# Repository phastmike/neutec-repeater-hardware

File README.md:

# Guia do projecto Repetidor Neutec

Este documento visa guiar e documentar o projecto Repetidor Neutec.

## Enquadramento

O projecto surge de um contacto informal do Costa (**CT1EYN**) comigo
(**CT1ENQ**), cujo objectivo inicial seria documentar a parte de controlo que o
Costa (**CT4QC**) fez no repetidor de UHF de Guimarães para posteriormente as 
aplicar num repetidor de origem da Neutec que não cumpria os requisitos legais.

Quando referimos o Costa (**CT4QC**), também devemos incluir o Armindo
(**CT1AND**) e outros que eventualmente tenham participado no esforço de munir a
ARM (Associação de Rádioamadores do Minho) de um conjunto de repetidores de
"construção caseira".

Como não privei nem tive grande contacto com os membros da ARM desse período,
além de ter estado ausente da região por vários anos, acabo por desconhecer a
história dos bastidores técnicos da associação. Entretanto, infelizmente, quem 
detinha o conhecimento acabou por falecer (sk).

### Um pouco de história

Através de um documento anexo ao repetidor de Guimarães conseguimos apurar a
data de Setembro 1998 pelo que terá sido por essa altura que o repetidor estaria
pronto para ser instalado. Este repetidor era um rádio Neutec SM-1630U (UHF)
modificado para servir como repetidor. O emissor e receptor funcionam em
simultâneo e essa modificação não foi documentada, nem na altura, nem agora.
Também foi introduzida alguma electrónica para controlo de transmissão, 
identificação em morse com intervalo de 10 minutos entre outros.
Posteriormente, teve nova intervenção para cumprir os novos requisitos de
identificação de voz. Estas adições são o alvo da nossa documentação.

Inicialmente o indicativo do repetidor era **CT0UGM** na frequência de 
**439.100 MHz**, RU88, e com a alteração da legislação, passou a ter o
indicativo **CQ0UGMR**, RU728, até aos dias de hoje.

### O início do projecto

Volvidos estes anos todos e havendo no legado da ARM, um repetidor de origem da
Neutec (SM-1645HS) para os 2m (VHF), operacional mas sem tom de protecção e sem 
identificação, fazia todo o sentido perceber o que foi feito no repetidor de 
Guimarães e replicar, dentro das diferenças existentes, algo similar para dotar
a ARM de um repetidor que pudesse servir de substituto ou mesmo para uma nova
instalação. 

Havendo essa necessidade e com a pandemia que nos afectou desde 2019 até à
actualidade (estamos em 2021) houve um novo fôlego na comunidade de 
rádioaamadores e o Costa (**CT1EYN**) lançou o desafio que foi aceite.

Infelizmente só tivemos acesso ao repetidor Neutec já na fase final do projecto
pelo que haveria lugar a algumas melhorias adicionais, ainda assim, foi obtido
um bom resultado e estamos em testes finais faltando apenas os testes de campo
na montanha da Santa Marta, no local do repetidor.

## Requisitos

Legalmente, em Portugal, um repetidor para o serviço de amador deve cumprir um
conjunto de requisitos. Do ponto de vista de controlo, são os seguintes:

- Tempo de retransmissão - Timeout Timer: Max 3 min (180s)
- Tempo de penalização - Retrigger/Penalty: 5 seg.
- Intervalo de identificação - ID Interval: Max 10 min (600s)

Requisito adicional, será o de evitar que a identificação ocorra quando alguém
está a utilizar o repetidor evitando assim que duas vozes concorram pela atenção
. Além disso deve contemplar a utilização do microfone de mão, no próprio
repetidor e evitar que não haja identificação durante um período de bloqueio
("timeout"). Este requisito levanta uma questão em particular, a da
obrigatoriedade de se identificar de 10 em 10 minutos. No entanto, a lei deve,
na minha opinião, ser entendida ao invés de uma interpretação cega. Assim; 
do ponto de vista da nossa actividade, faz todo o sentido, identificar o
repetidor, intervaladamente, para que eventuais escutas,quando não haja 
actividade no repetidor, consigam identificar o mesmo.
Se a identificação ocorrer em simultâneo com um QSO, em nada será benéfico, 
tanto é que este requisito se coloca. Do ponto de vista informativo, a presença
de um QSO implica a identificação dos intervinientes que por sua vez identifica
indirectamente o repetidor que por sua vez aguardará de forma incessante, a
possibilidade de se identificar, se é que podemos dizê-lo desta forma. Se a 
identificação ocorre no primeiro instante em que está livre ou se após uma
análise mais ou menos cuidada, o resultado obtido, será sempre no intuito de
seguir a lei mas salvaguardando a "qualidade" de um qso.

## Primeira análise

O primeiro passo do projecto foi efectuar engenharia reversa nos circuitos de
controlo construídos pelo Costa (**CT4QC**) por forma a desenhar um esquema e
posterior compreensão dos passos dados na altura. 

O repetidor de Guimarães foi construído com montagem de superfície utilizando
componentes THT, com PCB cortados "à mão" e placas de furos genéricas. Além
disso, estão divididos em dois "conjuntos" que para simplicidade passaremos a
designar por:

- Placa de cima
- Placa de baixo

Esta designação tem em consideração o posicionamente dos circuitos na montagem
original que foi mantida.

### Placa de baixo

Na placa de baixo temos vários blocos:

- Detecção de sub-tom
- Controlo de PTT
- Temporização de cauda
- Temporização de retransmissão

### Placa de cima

Na placa de cima temos os blocos referentes à identificação:

- microcontrolador
 - temporizador de 10min.
 - verificação de tom e ou PTT
 - disparo da identificação Voz/Morse
- controlo de PTT da identificação
- gerador de sinal áudio de Morse

## Organização do projecto

Após esta breve explicação, convém descrever a organização da documentação
relativa ao projecto. 

O projecto é na realidade um conjunto de projectos:

- Desenho dos esquemas do repetidor original
- Novo projecto de repetidor baseado no anterior, inclui PCBs e novo *firmware*
- Adaptação do desenho original, no repetidor de Guimarães com as alterações
realizadas ao esquema inicial.
- Vários (documentos, *datasheets*, imagens, etc)

## Descrição detalhada

Segue uma descrição, mais detalhada, das várias pastas deste projecto.

### [CT1ENQ_CT1EYN](./CT1ENQ_CT1EYN/)

As novas placas, esquemas e firmware.

- [Placa de baixo](./CT1ENQ_CT1EYN/bottom)
- [Placa de cima](./CT1ENQ_CT1EYN/top)
- [Novo firmware e código fonte (AT89C2051)](./CT1ENQ_CT1EYN/firmware)
- [Manual](./CT1ENQ_CT1EYN/manual)

### [CT4QC](./CT4QC)

O esquema original das adições que foram feitas ao SM-1630U para o dotar de
controlo de repetidor (baseado no repetidor de UHF de Guimarães). Também inclui
os esquemas das alterações que foram feitas ao original e uma "imagem" do
código original (binário). O firmware para esta modificação está anexa ao
novo *firmware* do repetidor.

- [Esquema de baixo](./CT4QC/original/bottom)
- [Esquema de cima](./CT4QC/original/top)
- [Esquema das novas modificações (cima)](./CT4QC/mod/)
- [*Firmware* original do AT89C2051](./CT4QC/original/firmware)

#### [Tools](./tools)

Programas auxiliares para cálculo de valores no temporizador e detector de tom.
Contém tabelas de valores em pdf.

#### [Doc](./doc/)
  
Conjunto de documentos reunidos durante o desenrolar do projecto, uns mais
relevantes do que outros (Datasheets, Papers, Pdfs, etc).

**Esta pasta não deverá estar presente nos repositórios públicos**.

#### [Images](./images/)

Imagens relacionadas com o projecto.

**Esta pasta não deverá estar presente nos repositórios públicos**.

#### [Sound](./sound/)

Ficheiros de áudio, utilizados no projecto (identificação).

## Software, *Frameworks* e outras informações

O trabalho foi projectado na sua totalidade num sistema Linux (Fedora 34) no
entanto existem as mesmas ferramentas ou equivalentes para o sistema Windows.

No desenho de esquemas e placas de circuito impresso, foi utilizado o
software gratuito, [KiCad 5.1.10-1](https://www.kicad.org).

O firmware foi desenvolvido em linguagem C e foi utilizado o compilador **sdcc**
, [Small Devices C Compiler](http://sdcc.sourceforge.net/) (v4.0.0) juntamente
com **Makefiles**.

Para programar o microcontrolador AT89C2051, utilizamos o programador
[TL866II Plus](http://www.autoelectric.cn/en/tl866_main.html) e o programa
[**minipro** (linux)](https://gitlab.com/DavidGriffith/minipro/).

## Notas finais

Os projectos devem ter documentos descritivos dentro de cada pasta, sempre que
se justificar.

Também convém indicar que o projecto de firmare (código fonte), quando num
contexto de repositório público, terá o seu repositório próprio. Já os esquemas
e restantes ficheiros estarão a acompanhar este documento. Num contexto interno
à ARM ou da comunidade de rádioamadores local, os ficheiros estarão todos 
agregados, num formato de compressão comum.

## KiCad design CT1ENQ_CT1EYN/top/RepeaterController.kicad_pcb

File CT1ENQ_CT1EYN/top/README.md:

# Neutec Repetidor/Repeater

## PCB Assembly and fitting notes

After assembly, Costa's 555 (Motorola) was erratic at best (bad pin connection?). Changed it for a Philips one and problem solved. Repeater was not ungrabbing the PTT line at the end of transmition (id). The PTT sense circuit is very sensible. Adding a 100nf/10nf capacitor at the main J connector (8 pin molex) pin1 (ID_PTT) did improve the result. Also the ISD play auto ptt key up saw the 100uf removed. Probably it's not even needed or if added then a lower value, eventually a ceramic cap would suffice.

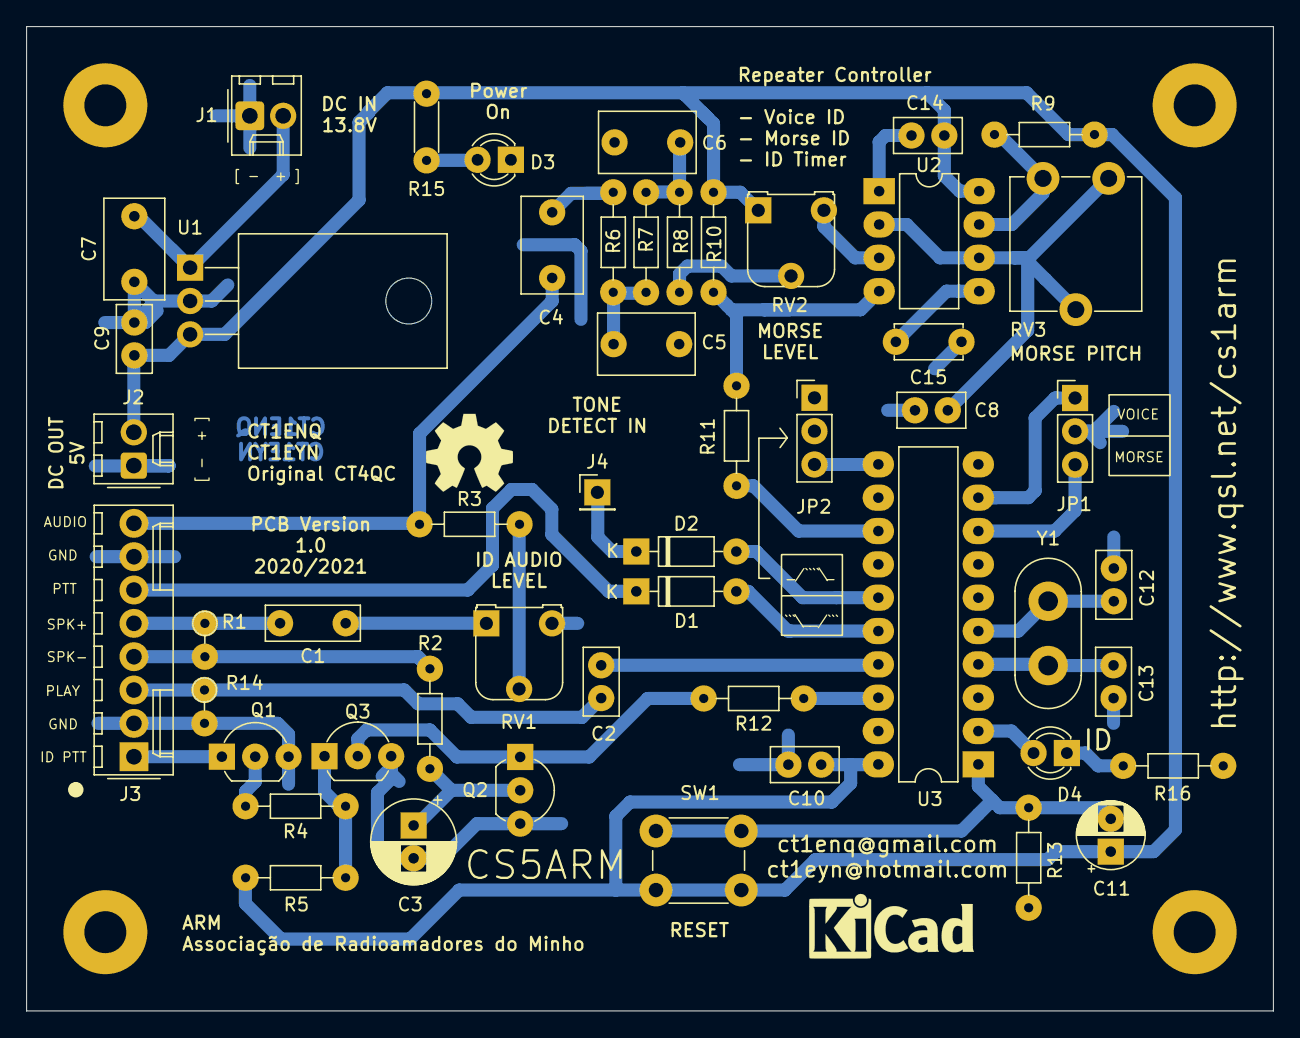
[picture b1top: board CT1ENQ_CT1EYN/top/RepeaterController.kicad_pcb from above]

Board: 2 copper layers, 95.0 x 75.0 mm, 52 parts (0 on the bottom side), 39 nets.

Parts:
C1: 4n7; C_Disc_D7.0mm_W2.5mm_P5.00mm
C2, C8, C9, C10, C14: 100n; C_Disc_D5.0mm_W2.5mm_P2.50mm
C3: 100u/16V; CP_Radial_D6.3mm_P2.50mm
C4, C5, C6: 22n; C_Rect_L7.2mm_W4.5mm_P5.00mm_FKS2_FKP2_MKS2_MKP2
C7: 470n; C_Disc_D7.5mm_W4.4mm_P5.00mm
C11: 10u/50V; CP_Radial_D5.0mm_P2.50mm
C12, C13: 33p; C_Disc_D5.0mm_W2.5mm_P2.50mm
C15: 10n; C_Disc_D5.0mm_W2.5mm_P5.00mm
D1, D2: 1N4148; D_DO-35_SOD27_P7.62mm_Horizontal
D3, D4: LED; LED_D3.0mm
J1, J2: Conn_01x02; Molex_KK-254_AE-6410-02A_1x02_P2.54mm_Vertical
J3: Conn_01x08; Molex_KK-254_AE-6410-08A_1x08_P2.54mm_Vertical
J4: Tone Detector; PinHeader_1x01_P2.54mm_Vertical
JP1: ID TYPE(None/Either/Both?); PinHeader_1x03_P2.54mm_Vertical
JP2: PLAY L2H or H2L; PinHeader_1x03_P2.54mm_Vertical
Q1: BC548B; TO-92_Inline_Wide
Q2: BC548; TO-92_Inline_Wide
Q3: BC548C; TO-92_Inline_Wide
R1: 27; R_Axial_DIN0204_L3.6mm_D1.6mm_P2.54mm_Vertical
R2, R16: 1k; R_Axial_DIN0204_L3.6mm_D1.6mm_P7.62mm_Horizontal
R3, R9: 10k; R_Axial_DIN0204_L3.6mm_D1.6mm_P7.62mm_Horizontal
R4: 3k9; R_Axial_DIN0204_L3.6mm_D1.6mm_P7.62mm_Horizontal
R5, R10: 4k7; R_Axial_DIN0204_L3.6mm_D1.6mm_P7.62mm_Horizontal
R6: 680; R_Axial_DIN0204_L3.6mm_D1.6mm_P7.62mm_Horizontal
R7, R8: 820; R_Axial_DIN0204_L3.6mm_D1.6mm_P7.62mm_Horizontal
R11: 120; R_Axial_DIN0204_L3.6mm_D1.6mm_P7.62mm_Horizontal
R12: 4K7; R_Axial_DIN0204_L3.6mm_D1.6mm_P7.62mm_Horizontal
R13: 8k2; R_Axial_DIN0204_L3.6mm_D1.6mm_P7.62mm_Horizontal
R14: 10k; R_Axial_DIN0204_L3.6mm_D1.6mm_P2.54mm_Vertical
R15: 1k; R_Axial_DIN0204_L3.6mm_D1.6mm_P5.08mm_Horizontal
RV1: 50k; Potentiometer_Runtron_RM-065_Vertical
RV2: 6k8; Potentiometer_Runtron_RM-065_Vertical
RV3: 22k; Potentiometer_ACP_CA9-V10_Vertical
SW1: RESET; SW_PUSH_6mm_H4.3mm
U1: L7805; TO-220-3_Horizontal_TabDown
U2: NE555P; DIP-8_W7.62mm_LongPads
U3: AT89C2051-24PU; DIP-20_W7.62mm_LongPads
Y1: 4MHz; Crystal_HC50_Vertical

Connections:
+5V: C9.2, C10.1, C11.1, C14.1, J2.2, R5.1, R9.1, R10.1, R15.1, RV2.1, SW1.2, U1.3, U2.8, U3.20
Audio: C4.1, J3.8, R3.1
GND: C3.2, C5.2, C6.2, C7.1, C8.2, C9.1, C10.2, C12.2, C13.2, C14.2, C15.2, D3.1, J1.1, J2.1, J3.2, J3.7, JP1.2, JP2.1, JP2.2, Q1.3, Q2.3, Q3.3, R13.2, R14.2, R16.2, RV1.3, U1.2, U2.1, U3.10
ID_PTT: J3.1, Q1.1
ISD_PLAY: C2.2, J3.3, R14.1
ISD_SPK+: C1.2, J3.5, R1.1
ISD_SPK-: J3.4, R1.2, R2.2
unnamed: C1.1, RV1.1
unnamed: C2.1, U3.17
unnamed: C3.1, Q2.2, R2.1
unnamed: C4.2, R6.1
unnamed: C5.1, R6.2, R7.1
unnamed: C6.1, R7.2, R8.1
unnamed: C8.1, RV3.2, RV3.3, U2.2, U2.6
unnamed: C11.2, R13.1, SW1.1, U3.1
unnamed: C12.1, U3.5, Y1.1
unnamed: C13.1, U3.4, Y1.2
unnamed: C15.1, U2.5
unnamed: D3.2, R15.2
unnamed: D4.1, R16.1
unnamed: D4.2, U3.2
unnamed: JP1.1, U3.9
unnamed: JP1.3, U3.8
unnamed: JP2.3, U3.11
unnamed: Q1.2, R4.2
unnamed: Q2.1, Q3.2, R12.2
unnamed: Q3.1, R4.1, R5.2
unnamed: R3.2, RV1.2
unnamed: R8.2, RV2.2
unnamed: R9.2, RV3.1, U2.7
unnamed: R10.2, R11.1, U2.4
unnamed: R11.2, U3.13
unnamed: R12.1, U3.18
unnamed: RV2.3, U2.3
PTT: D1.1, J3.6
PTT_IN: D1.2, U3.16
TONE_IN: D2.2, U3.15
ToneDetector: D2.1, J4.1
VCC: C7.2, J1.2, U1.1

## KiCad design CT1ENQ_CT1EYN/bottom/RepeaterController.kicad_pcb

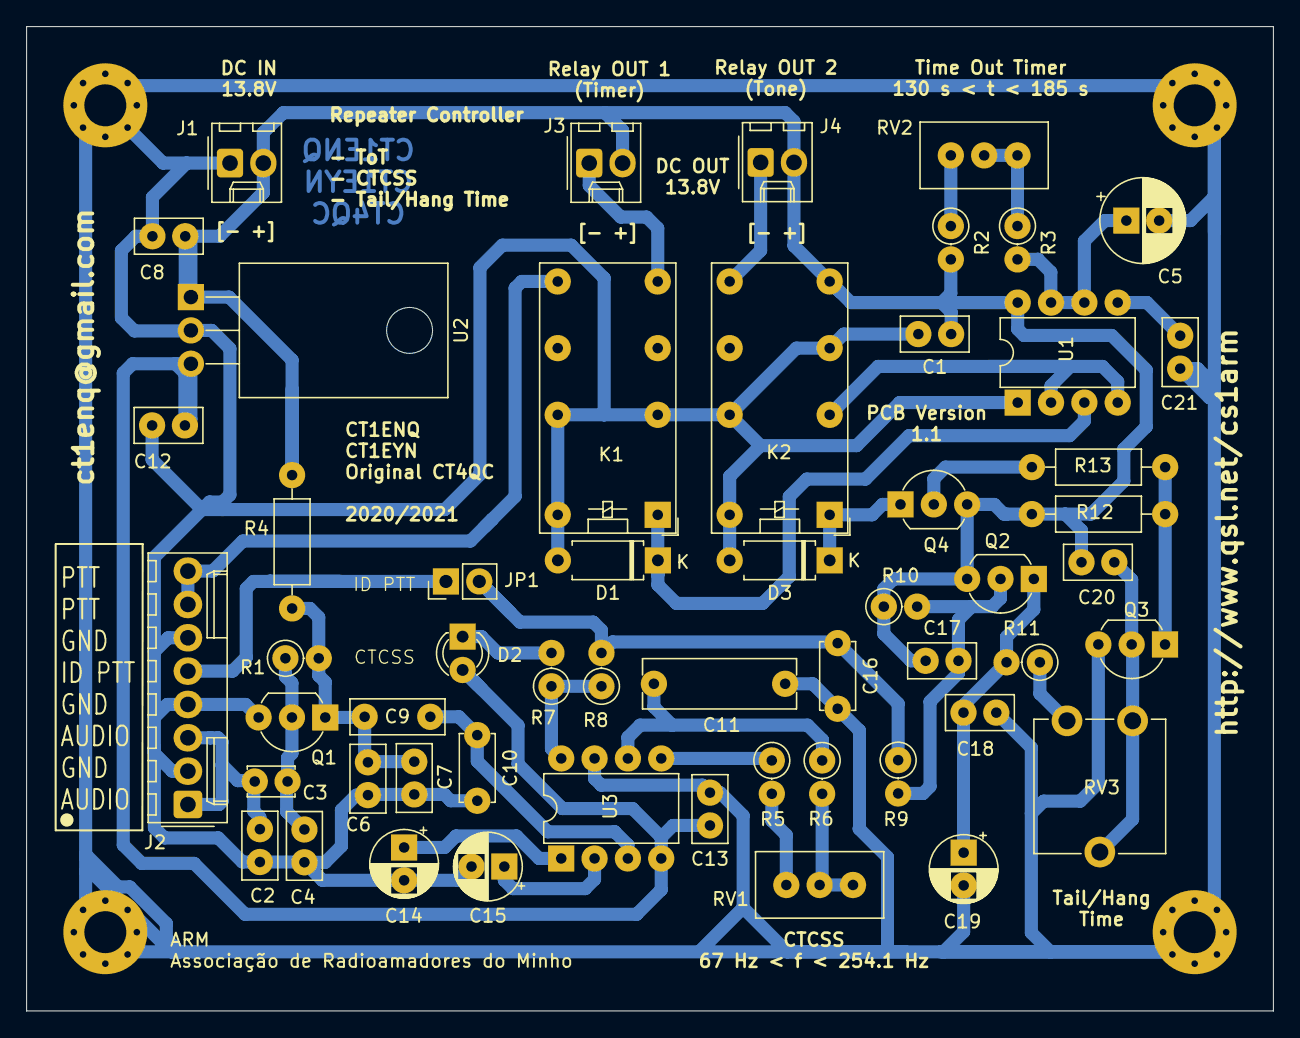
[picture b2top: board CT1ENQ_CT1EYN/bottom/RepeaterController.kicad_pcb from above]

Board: 2 copper layers, 95.0 x 75.0 mm, 54 parts (0 on the bottom side), 33 nets.

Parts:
C1, C2, C13: 330p; C_Disc_D5.0mm_W2.5mm_P2.50mm
C3: 1u; C_Disc_D3.4mm_W2.1mm_P2.50mm
C4, C7, C18, C20: 27p; C_Disc_D5.0mm_W2.5mm_P2.50mm
C5: 47u/25V; CP_Radial_D6.3mm_P2.50mm
C6: 100n; C_Disc_D5.0mm_W2.5mm_P2.50mm
C8: 0.33u; C_Disc_D5.0mm_W2.5mm_P2.50mm
C9: 470n; C_Disc_D7.0mm_W2.5mm_P5.00mm
C10: 330p; C_Disc_D5.0mm_W2.5mm_P5.00mm
C11: 100n Polyester; C_Rect_L11.5mm_W3.6mm_P10.00mm_MKT
C12: 0.1u; C_Disc_D5.0mm_W2.5mm_P2.50mm
C14: 47u/25V; CP_Radial_D5.0mm_P2.50mm
C15: 1u/25V; CP_Radial_D5.0mm_P2.50mm
C16: 27p; C_Disc_D5.0mm_W2.5mm_P5.00mm
C17: 2.2n; C_Disc_D5.0mm_W2.5mm_P2.50mm
C19: 2.2u/25V; CP_Radial_D5.0mm_P2.50mm
C21: 10n *; C_Disc_D5.0mm_W2.5mm_P2.50mm
D1, D3: 1N4148/1N4001; D_A-405_P7.62mm_Horizontal
D2: LED 3mm; LED_D3.0mm
J1, J3, J4: Conn_01x02; Molex_KK-254_AE-6410-02A_1x02_P2.54mm_Vertical
J2: Conn_01x08; Molex_KK-254_AE-6410-08A_1x08_P2.54mm_Vertical
JP1: Jumper; PinHeader_1x02_P2.54mm_Vertical
K1, K2: G5V-2 (Matsushita DSBT2-S-DC12V); Relay_DPDT_Omron_G5V-2
Q1, Q3: BC548B; TO-92_Inline_Wide
Q2: BC558C; TO-92_Inline_Wide
Q4: BC327; TO-92_Inline_Wide
R1, R3: 1.5M; R_Axial_DIN0207_L6.3mm_D2.5mm_P2.54mm_Vertical
R2: 1M; R_Axial_DIN0207_L6.3mm_D2.5mm_P2.54mm_Vertical
R4: 15k; R_Axial_DIN0207_L6.3mm_D2.5mm_P10.16mm_Horizontal
R5: 33k; R_Axial_DIN0207_L6.3mm_D2.5mm_P2.54mm_Vertical
R6: 2k7; R_Axial_DIN0207_L6.3mm_D2.5mm_P2.54mm_Vertical
R7: 150; R_Axial_DIN0207_L6.3mm_D2.5mm_P2.54mm_Vertical
R8: 1k8; R_Axial_DIN0207_L6.3mm_D2.5mm_P2.54mm_Vertical
R9: 2k2; R_Axial_DIN0207_L6.3mm_D2.5mm_P2.54mm_Vertical
R10: 100k; R_Axial_DIN0207_L6.3mm_D2.5mm_P2.54mm_Vertical
R11: 100; R_Axial_DIN0207_L6.3mm_D2.5mm_P2.54mm_Vertical
R12: 10k; R_Axial_DIN0207_L6.3mm_D2.5mm_P10.16mm_Horizontal
R13: 1k8; R_Axial_DIN0207_L6.3mm_D2.5mm_P10.16mm_Horizontal
RV1: 100k; Potentiometer_Bourns_3296W_Vertical
RV2: 1M; Potentiometer_Bourns_3296W_Vertical
RV3: 22k; Potentiometer_ACP_CA9-V10_Vertical
U1: NE555D; DIP-8_W7.62mm
U2: L7805; TO-220-3_Horizontal_TabDown
U3: NE567; DIP-8_W7.62mm

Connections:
+5V: C12.1, C13.1, D2.2, U2.3, U3.4
+12V: C1.1, C8.1, C17.1, C20.1, J1.2, J3.2, J4.2, K2.8, Q2.3, Q4.3, R2.2, R4.1, R10.1, R12.2, U1.8, U2.1
GND: C1.2, C2.2, C4.2, C5.2, C6.2, C7.2, C8.2, C10.2, C11.2, C12.2, C13.2, C14.2, C15.2, C16.2, C18.2, C19.2, C21.2, D1.2, D3.2, J1.1, J2.2, J2.4, J2.6, K1.4, K1.13, K1.16, K2.6, K2.13, K2.16, Q1.3, Q3.3, U1.1, U2.2, U3.7
unnamed: C3.1, C4.1, Q1.2, R1.1
unnamed: C5.1, R3.2, U1.6, U1.7
unnamed: C6.1, C7.1, C9.2, Q1.1, R1.2, R4.2
unnamed: C9.1, C10.1, U3.3
unnamed: C11.1, R6.1, U3.6
unnamed: C14.1, U3.1
unnamed: C15.1, U3.2
unnamed: C16.1, JP1.2, R8.2, R9.1
unnamed: C17.2, Q2.2, R9.2, R10.2
unnamed: C18.1, C19.1, Q2.1, R11.2
unnamed: C20.2, Q3.2, RV3.2, RV3.3
unnamed: C21.1, U1.5
unnamed: D1.1, K1.1, U1.3
unnamed: D2.1, R7.2
unnamed: D3.1, K2.1, Q4.1
unnamed: J3.1, K1.8
unnamed: J4.1, K2.9
unnamed: Q3.1, R12.1, R13.1
unnamed: Q4.2, R13.2
unnamed: R2.1, RV2.1
unnamed: R3.1, RV2.2, RV2.3
unnamed: R5.1, U3.5
unnamed: R5.2, RV1.1
unnamed: R6.2, RV1.2, RV1.3
unnamed: R7.1, R8.1, U3.8
unnamed: R11.1, RV3.1
PTT: J2.7, J2.8, K1.9
RX_Audio: C2.1, C3.2, J2.1, J2.3
TIMER_CTRL: K2.4, U1.2, U1.4
ToneDetector: J2.5, JP1.1

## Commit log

2021-07-08 Exported schematics for CT4KQ folder
2021-07-22 Changes to gitignore and added manual (VHF repeater - SM1645HS). PDF from gnome marker export
2021-07-22 Added link to recently added manual
2021-07-24 minor fixes
2021-12-13 Added ID files to sound folder
